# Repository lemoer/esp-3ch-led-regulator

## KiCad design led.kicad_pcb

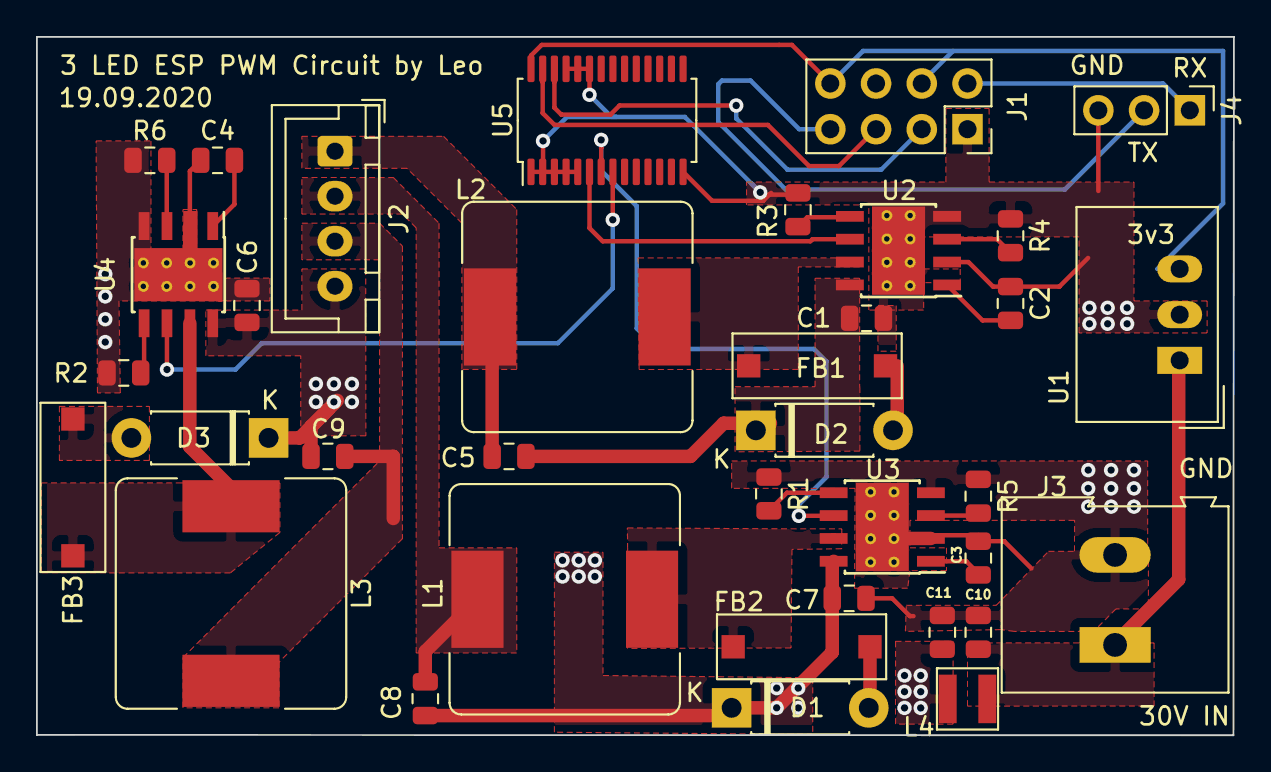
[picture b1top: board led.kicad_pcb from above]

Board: 2 copper layers, 66.5 x 38.8 mm, 36 parts (0 on the bottom side), 29 nets.

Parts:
C1, C6, C7, C10, C11: 2.2u; C_0805_2012Metric
C2, C3, C4, C5, C8, C9: 1u; C_0805_2012Metric
D1, D2, D3: SR106; D_DO-41_SOD81_P7.62mm_Horizontal
FB1, FB2, FB3: SMB/002; smb002
J1: Conn_02x04_Odd_Even; PinSocket_2x04_P2.54mm_Vertical
J2: Conn_01x04_Female; JST_XH_B4B-XH-A_1x04_P2.50mm_Vertical
J3: Conn_01x02_Female; TerminalBlock_Altech_AK300-2_P5.00mm
J4: Conn_01x03_Male; PinHeader_1x03_P2.54mm_Vertical
L1, L2, L3: 470u; L_Bourns_SRR1260
L4: 10u; 1212fps
R1, R2, R3: Rfs; R_0805_2012Metric
R4, R5, R6: Radj; R_0805_2012Metric
U1: TSR_0.5-2433; Converter_DCDC_TRACO_TSR-1_THT
U2, U3, U4: TPS92511; Texas_HSOP-8-1EP_3.9x4.9mm_P1.27mm_ThermalVias
U5: PCA9685PW; TSSOP-28_4.4x9.7mm_P0.65mm

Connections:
3V3: J1.4, J1.8, U1.3, U5.28
GND: C1.1, C2.1, C3.1, C4.1, C6.1, C7.1, C10.1, C11.1, J1.1, J3.2, J4.3, R1.1, R2.1, R3.1, R4.1, R5.1, R6.1, U1.2, U2.2, U2.4, U2.9, U3.2, U3.4, U3.9, U4.2, U4.4, U4.9, U5.1, U5.2, U5.3, U5.4, U5.5, U5.14, U5.23, U5.24, U5.25
GPIO0: J1.3, U5.26
GPIO2: J1.5, U5.27
LED_BLUE-: C9.1, J2.3, L3.2
LED_GREEN-: C8.1, J2.2, L1.2
LED_RED-: C5.1, J2.1, L2.2
unnamed: C2.2, U2.1
unnamed: C3.2, U3.1
unnamed: C4.2, U4.1
unnamed: D1.2, FB2.1
unnamed: D2.2, FB1.1
unnamed: D3.2, FB3.1
unnamed: FB1.2, L2.1, U2.7
unnamed: FB2.2, L1.1, U3.7
unnamed: FB3.2, L3.1, U4.7
unnamed: R1.2, U3.5
unnamed: R2.2, U4.5
unnamed: R3.2, U2.5
unnamed: R4.2, U2.3
unnamed: R5.2, U3.3
unnamed: R6.2, U4.3
PWM_BLUE: U4.6, U5.8
PWM_GREEN: U3.6, U5.7
PWM_RED: U2.6, U5.6
RX: J1.7, J4.2
TX: J1.2, J4.1
VCC: C1.2, C5.2, C6.2, C7.2, C8.2, C9.2, C11.2, D1.1, D2.1, D3.1, J2.4, L4.1, U2.8, U3.8, U4.8
VCC_UNFILTERED: C10.2, J3.1, L4.2, U1.1

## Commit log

2020-09-19 initial attempt
